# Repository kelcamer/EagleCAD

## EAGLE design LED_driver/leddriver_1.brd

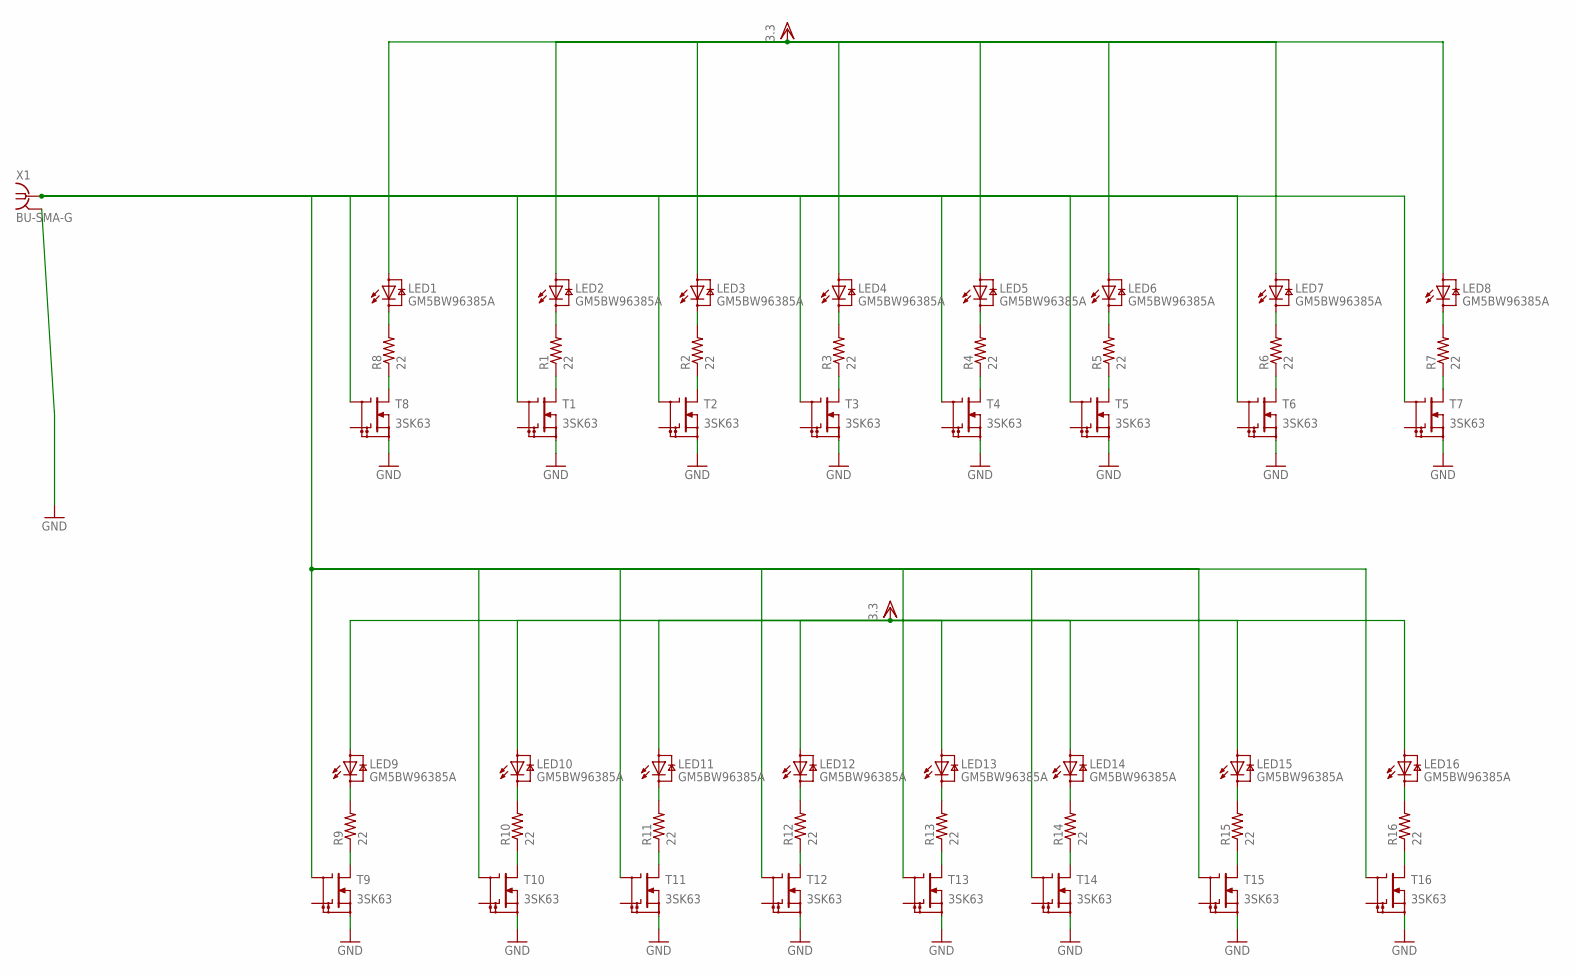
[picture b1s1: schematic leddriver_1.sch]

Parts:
LED1, LED2, LED3, LED4, LED5, LED6, LED7, LED8, LED9, LED10, LED11, LED12, LED13, LED14, LED15, LED16: GM5BW96385A
R1, R2, R3, R4, R5, R6, R7, R8, R9, R10, R11, R12, R13, R14, R15, R16: 22; 0207/5V
T1, T2, T3, T4, T5, T6, T7, T8, T9, T10, T11, T12, T13, T14, T15, T16: 3SK63; TO72
X1: BU-SMA-G

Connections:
GND: T1.4 (SOURCE), T2.4 (SOURCE), T3.4 (SOURCE), T4.4 (SOURCE), T5.4 (SOURCE), T6.4 (SOURCE), T7.4 (SOURCE), T8.4 (SOURCE), T9.4 (SOURCE), T10.4 (SOURCE), T11.4 (SOURCE), T12.4 (SOURCE), T13.4 (SOURCE), T14.4 (SOURCE), T15.4 (SOURCE), T16.4 (SOURCE), X1.2, X1.3 (2), X1.4 (2), X1.5 (2)
unnamed: R8.1, T8.1 (DRAIN)
unnamed: LED2.C, R1.2
unnamed: LED1.C, R8.2
unnamed: R1.1, T1.1 (DRAIN)
unnamed: LED3.C, R2.2
unnamed: R2.1, T2.1 (DRAIN)
unnamed: LED4.C, R3.2
unnamed: R3.1, T3.1 (DRAIN)
unnamed: LED5.C, R4.2
unnamed: R4.1, T4.1 (DRAIN)
unnamed: LED6.C, R5.2
unnamed: R5.1, T5.1 (DRAIN)
unnamed: LED7.C, R6.2
unnamed: R6.1, T6.1 (DRAIN)
unnamed: LED8.C, R7.2
unnamed: R7.1, T7.1 (DRAIN)
unnamed: LED9.C, R9.2
unnamed: R9.1, T9.1 (DRAIN)
unnamed: LED10.C, R10.2
unnamed: R10.1, T10.1 (DRAIN)
unnamed: LED11.C, R11.2
unnamed: R11.1, T11.1 (DRAIN)
unnamed: LED12.C, R12.2
unnamed: R12.1, T12.1 (DRAIN)
unnamed: LED13.C, R13.2
unnamed: R13.1, T13.1 (DRAIN)
unnamed: LED14.C, R14.2
unnamed: R14.1, T14.1 (DRAIN)
unnamed: LED15.C, R15.2
unnamed: R15.1, T15.1 (DRAIN)
unnamed: LED16.C, R16.2
unnamed: R16.1, T16.1 (DRAIN)
unnamed: T1.3 (G1), T2.3 (G1), T3.3 (G1), T4.3 (G1), T5.3 (G1), T6.3 (G1), T7.3 (G1), T8.3 (G1), T9.3 (G1), T10.3 (G1), T11.3 (G1), T12.3 (G1), T13.3 (G1), T14.3 (G1), T15.3 (G1), T16.3 (G1), X1.1
VDD: LED1.A, LED2.A, LED3.A, LED4.A, LED5.A, LED6.A, LED7.A, LED8.A, LED9.A, LED10.A, LED11.A, LED12.A, LED13.A, LED14.A, LED15.A, LED16.A

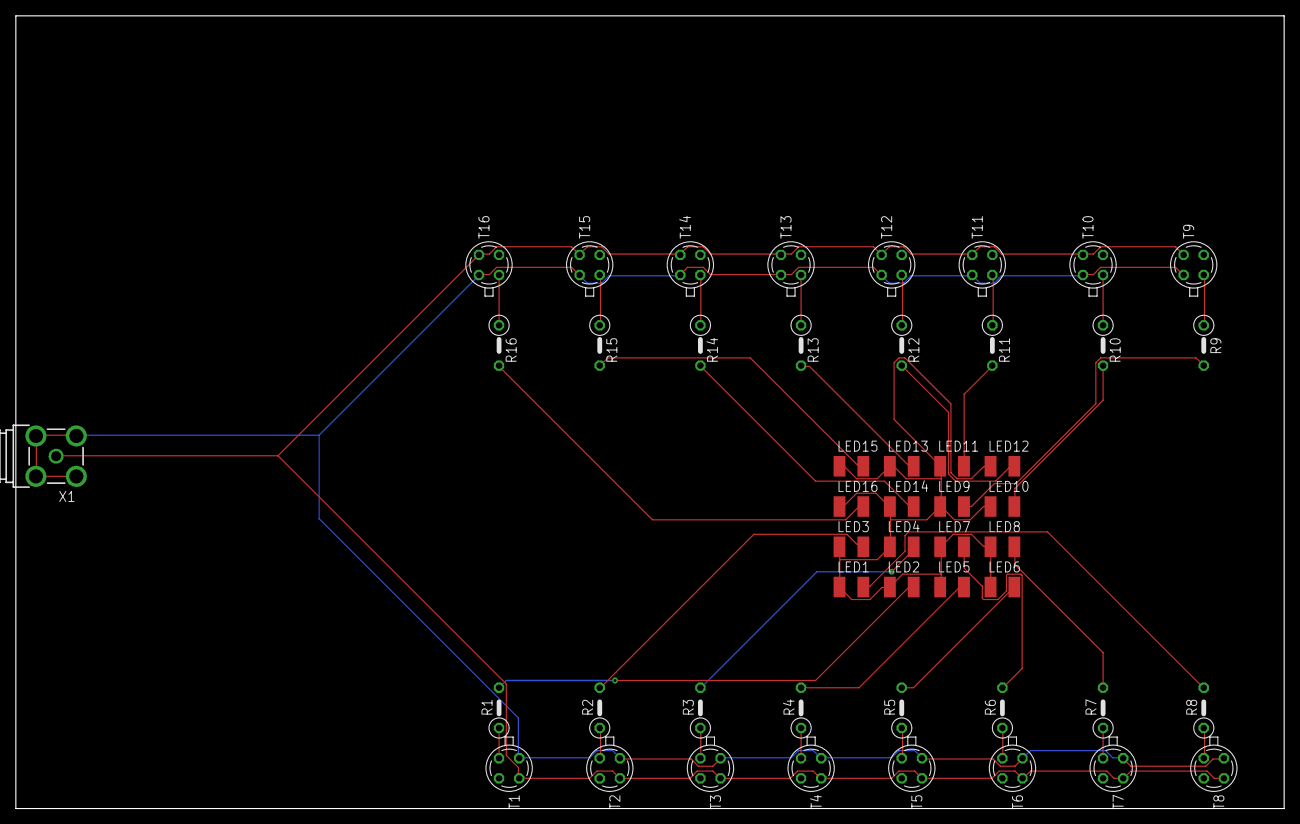
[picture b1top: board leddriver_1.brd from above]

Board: 2 copper layers, 160.0 x 100.0 mm, 49 parts (0 on the bottom side), 35 nets.

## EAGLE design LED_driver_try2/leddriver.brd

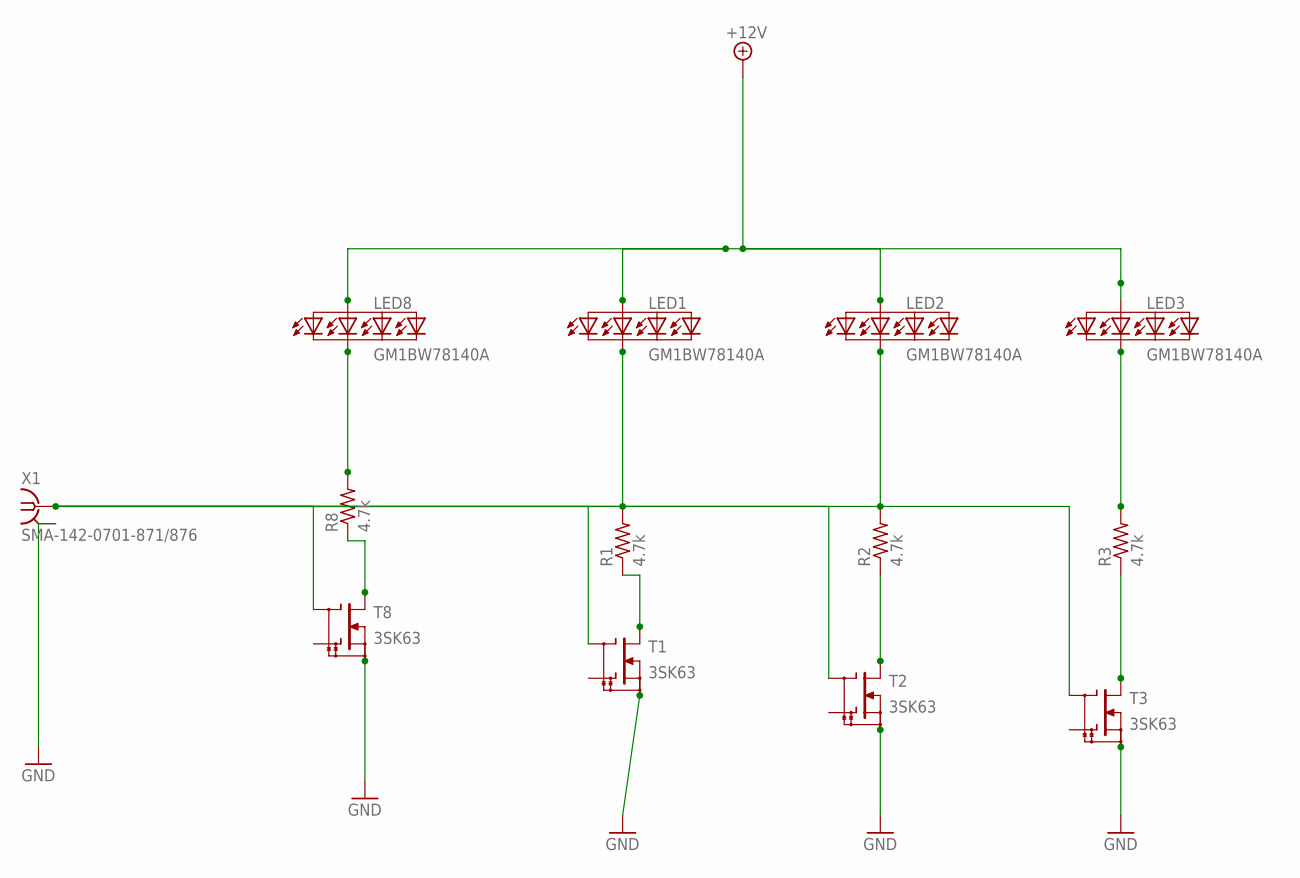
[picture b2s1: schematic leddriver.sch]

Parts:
LED1, LED2, LED3, LED8: GM1BW78140A
R1, R2, R3, R8: 4.7k; 0207/5V
T1, T2, T3, T8: 3SK63; TO72
X1: SMA-142-0701-871/876; J502-ND-142-0701-871/876

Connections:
+12V: LED1.A, LED2.A, LED3.A, LED8.A
GND: T1.4 (SOURCE), T2.4 (SOURCE), T3.4 (SOURCE), T8.4 (SOURCE), X1.G@1 (2), X1.G@2 (2), X1.G@3 (2), X1.G@4 (2)
unnamed: R8.1, T8.1 (DRAIN)
unnamed: R1.1, T1.1 (DRAIN)
unnamed: LED8.C, R8.2
unnamed: R2.1, T2.1 (DRAIN)
unnamed: LED1.C, R1.2
unnamed: R3.1, T3.1 (DRAIN)
unnamed: LED2.C, R2.2
unnamed: T1.3 (G1), T2.3 (G1), T3.3 (G1), T8.3 (G1), X1.1
unnamed: LED3.C, R3.2

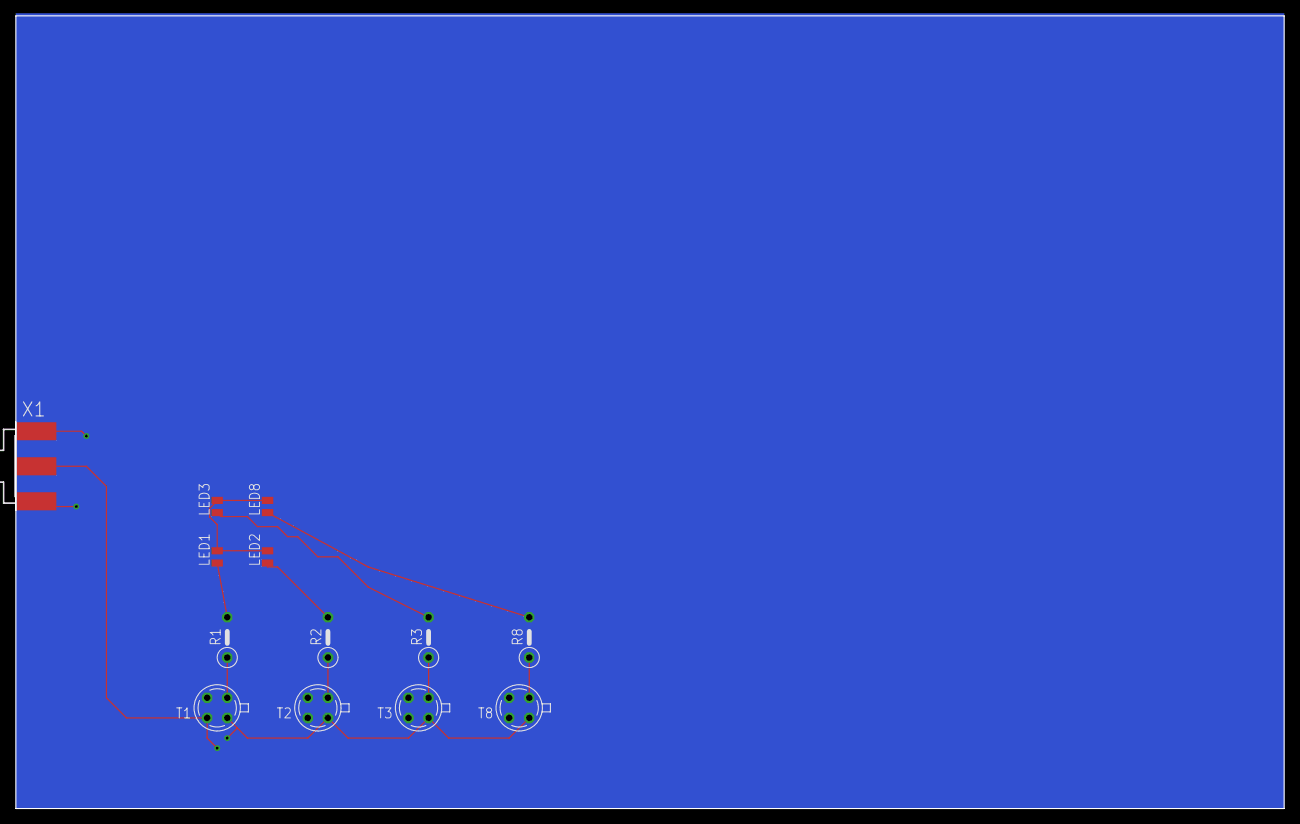
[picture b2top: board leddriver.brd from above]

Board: 2 copper layers, 160.0 x 100.0 mm, 13 parts (0 on the bottom side), 11 nets.

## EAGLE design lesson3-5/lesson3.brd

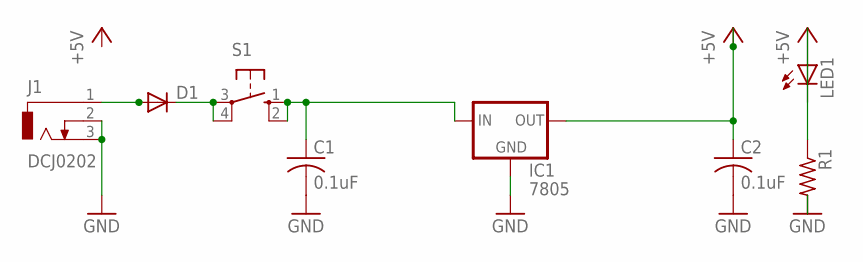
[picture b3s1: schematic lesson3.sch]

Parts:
C1, C2: 0.1uF; C025-030X050
D1: DIODE-D-7.5; D-7.5
IC1: 7805; 78XXL
J1: DCJ0202
LED1: LED5MM
R1: R-US_0204/5; 0204/5
S1: 10-XX; B3F-10XX

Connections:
+5V: C2.1, IC1.OUT
GND: C1.2, C2.2, IC1.GND, J1.2, J1.3, R1.2
unnamed: C1.1, IC1.IN, S1.1 (S), S1.2 (S1)
unnamed: LED1.K (C), R1.1
unnamed: D1.A, J1.1
unnamed: D1.C, S1.3, S1.4 (P1)

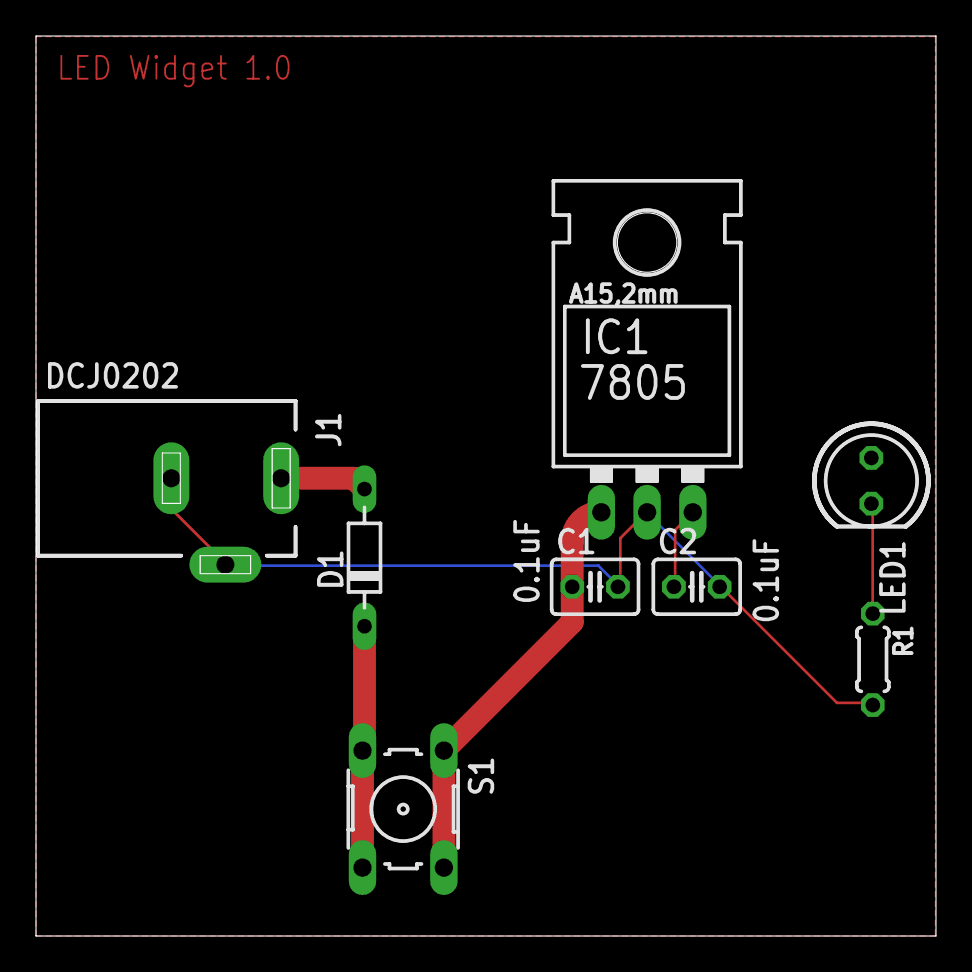
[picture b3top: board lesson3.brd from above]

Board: 2 copper layers, 50.0 x 50.0 mm, 8 parts (0 on the bottom side), 6 nets.

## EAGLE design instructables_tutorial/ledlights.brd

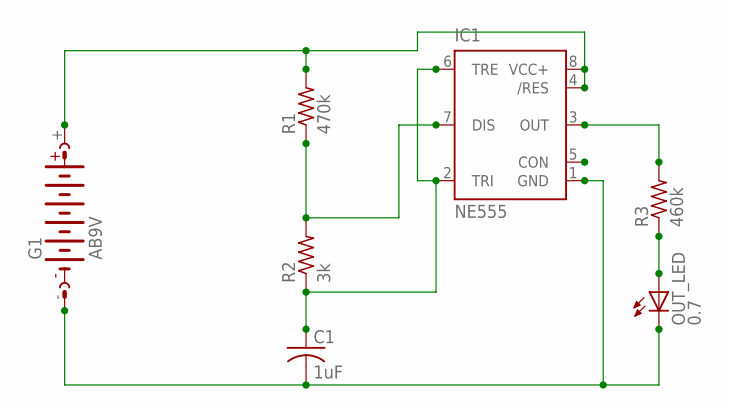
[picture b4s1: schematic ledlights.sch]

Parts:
C1: 1uF; C0805
G1: AB9V
IC1: NE555; DIL-08
OUT_LED: 0.7; CHIP-LED0805
R1: 470k; R0805
R2: 3k; R0805
R3: 460k; R0805

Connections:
unnamed: G1.+, IC1.4 (/RES), IC1.8 (VCC+), R1.2
unnamed: IC1.7 (DIS), R1.1, R2.2
unnamed: C1.1, IC1.2 (TRI), IC1.6 (TRE), R2.1
unnamed: C1.2, G1.-, IC1.1 (GND), OUT_LED.C
unnamed: IC1.3 (OUT), R3.2
unnamed: OUT_LED.A, R3.1

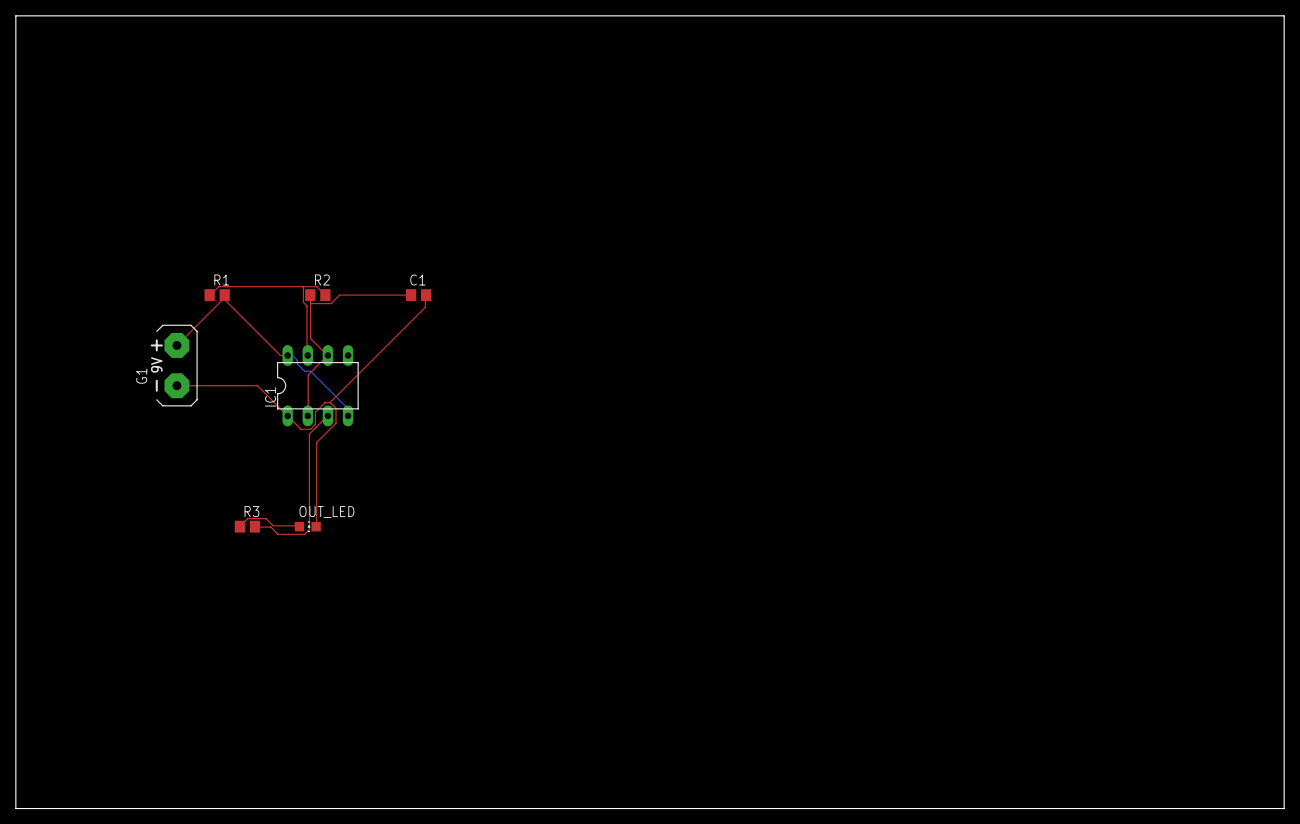
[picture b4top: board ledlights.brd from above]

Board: 2 copper layers, 160.0 x 100.0 mm, 7 parts (0 on the bottom side), 6 nets.

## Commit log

2017-10-04 Discrete Structures Homework
